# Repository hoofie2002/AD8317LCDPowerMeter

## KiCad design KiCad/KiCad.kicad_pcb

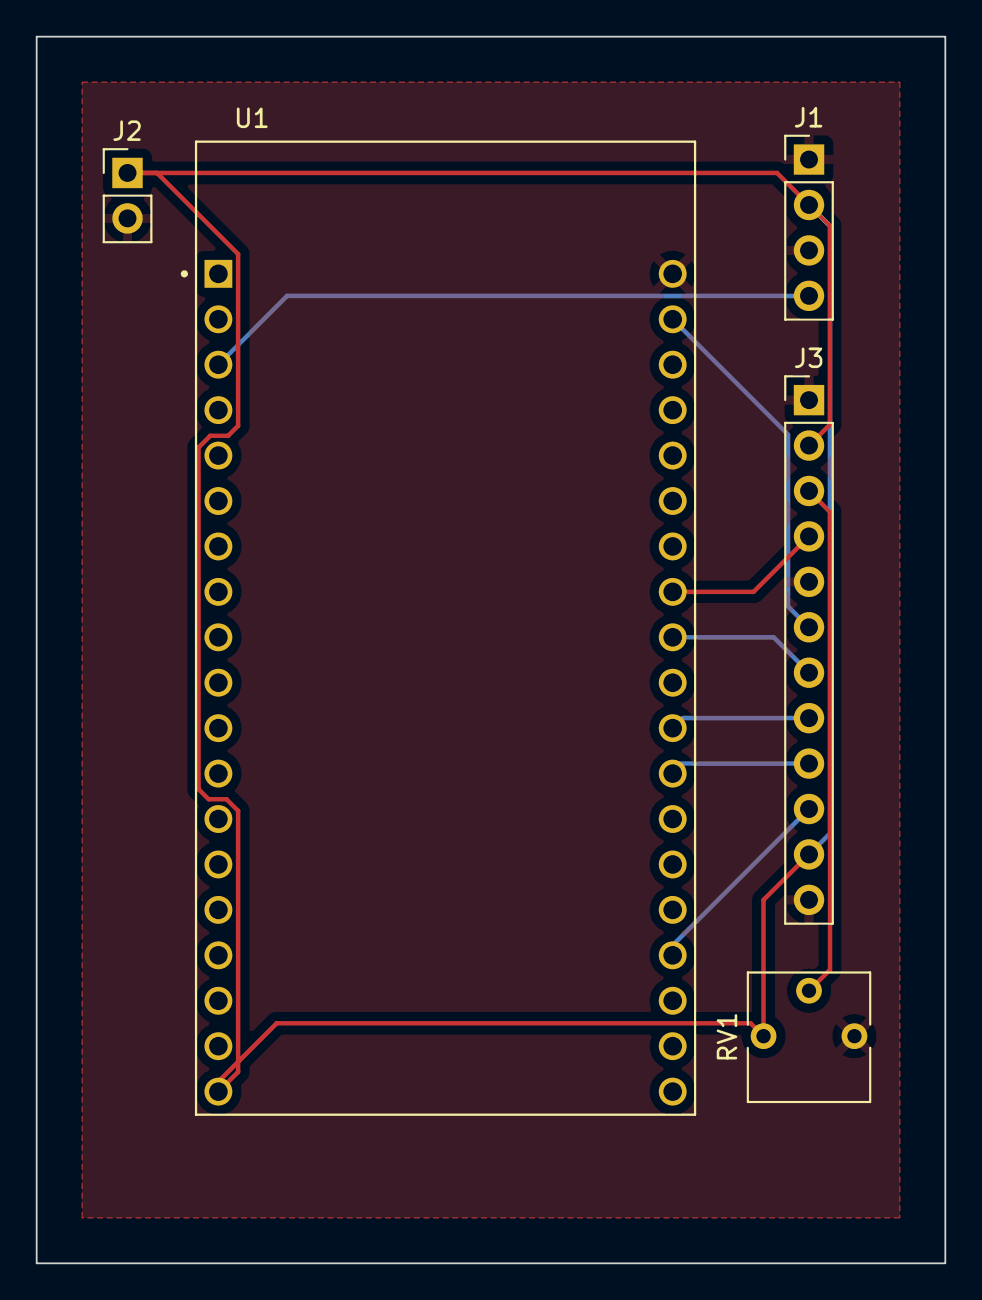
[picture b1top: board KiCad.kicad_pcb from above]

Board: 2 copper layers, 50.8 x 68.6 mm, 5 parts (0 on the bottom side), 10 nets.

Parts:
J1: Power; PinHeader_1x04_P2.54mm_Vertical
J2: AD8317; PinHeader_1x02_P2.54mm_Vertical
J3: LCD; PinHeader_1x12_P2.54mm_Vertical
RV1: Contrast; Potentiometer_Vishay_T73YP_Vertical
U1: ESP32; MODULE_ESP32-DEVKITC-32D

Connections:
+5V: J1.2, J2.1, J3.2, J3.11, RV1.3, U1.J2-19 (EXT_5V)
GND: J1.1, J1.3, J2.2, J3.1, J3.5, J3.12, RV1.1, U1.J3-1 (GND3)
unnamed: J1.4, U1.J2-3 (SENSOR_VP)
unnamed: J3.4, U1.J3-8 (IO19)
unnamed: J3.3, RV1.2
unnamed: J3.6, U1.J3-2 (IO23)
unnamed: J3.7, U1.J3-9 (IO18)
unnamed: J3.8, U1.J3-11 (IO17)
unnamed: J3.9, U1.J3-12 (IO16)
unnamed: J3.10, U1.J3-16 (IO15)

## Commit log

2023-05-07 Source and Kicad files
